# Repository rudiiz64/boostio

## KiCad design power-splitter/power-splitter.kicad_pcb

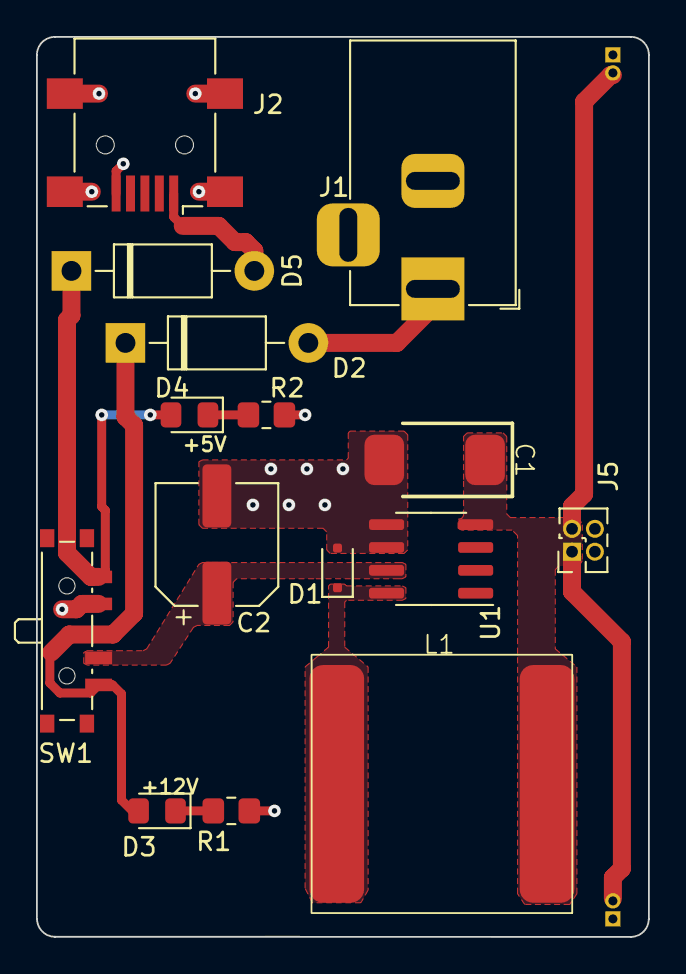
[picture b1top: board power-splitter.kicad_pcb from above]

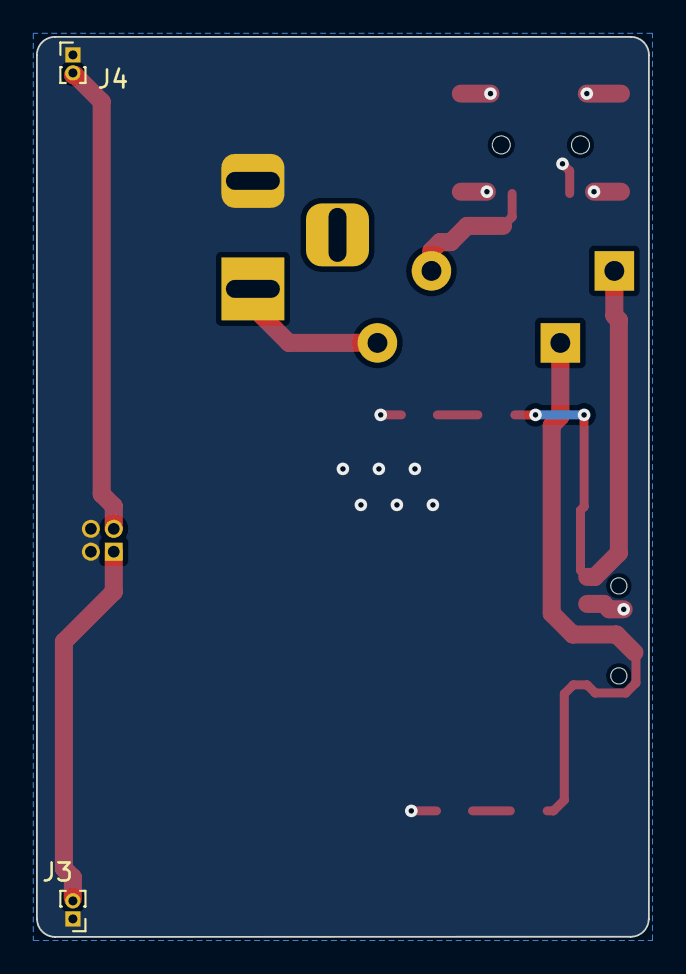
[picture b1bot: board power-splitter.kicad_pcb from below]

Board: 2 copper layers, 34.0 x 50.0 mm, 17 parts (2 on the bottom side), 9 nets.

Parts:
C1: 100u; 595DM_7.8x2.8mm
C2: 68u; CP_Elec_6.3x5.8
D1: SC-90; D_SOD-323F
D2, D5: 1N4007; D_DO-41_SOD81_P10.16mm_Horizontal
D3: +12V; LED_0805_2012Metric_Pad1.15x1.40mm_HandSolder
D4: +5V; LED_0805_2012Metric_Pad1.15x1.40mm_HandSolder
J1: Barrel_Jack; BarrelJack_Horizontal
J2: USB_B_Micro; USB_Mini-B_Lumberg_2486_01_Horizontal
J3, J4: Conn_01x02; PinHeader_1x02_P1.00mm_Vertical
J5: Conn_02x02_Counter_Clockwise; PinHeader_2x02_P1.27mm_Vertical
L1: 100u; SPM2007_LCI-37
R1, R2: 470; R_0805_2012Metric_Pad1.20x1.40mm_HandSolder
SW1: SW_SP3T; SW_SP3T_PCM13
U1: LM2594M-3.3; SOIC-8_3.9x4.9mm_P1.27mm

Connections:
+3V3: C1.1, J3.2, J4.2, J5.1, J5.2, L1.1, U1.4 (FB)
+5V: D4.2 (A), D5.1 (K), SW1.1
+12V: C2.1, D2.1 (K), D3.2 (A), SW1.3, SW1.4, U1.7 (VIN)
GND: C1.2, C2.2, D1.2 (A), J1.2, J2.5 (GND), J2.6 (Shield), J3.1, J4.1, J5.3, J5.4, R1.2, R2.2, SW1.2, U1.5 (~ON/OFF), U1.6 (GND)
unnamed: D1.1 (K), L1.2, U1.8 (OUT)
unnamed: D2.2 (A), J1.1
unnamed: D3.1 (K), R1.1
unnamed: D4.1 (K), R2.1
unnamed: D5.2 (A), J2.1 (VBUS)

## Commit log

2023-04-11 Updated to Rev 1.0
    + Finalized initial schematic
    + Initial PCB layout
    -- Layout needs work; unused copper area
2023-04-11 Updated Rev Number
2023-04-17 Updated layout
    + Adjusted ground pours
    + Adjusted power pours
2023-09-14 Updated schem/layout
    + Adjusted pours to filet edges
    + Added text for +3V3 outputs
    + Adjusted board edges to be less weird
2023-09-21 File clean up
2024-01-10 Updated to Rev B
    + Adjusted layout to be more compact and to fit on 51mm wide breadboards
    + Added 3D STEP files for the barrel jack, USB-Micro B receptacle
    + Added PDFs for the schematic and top/bottom layer of the PCB
